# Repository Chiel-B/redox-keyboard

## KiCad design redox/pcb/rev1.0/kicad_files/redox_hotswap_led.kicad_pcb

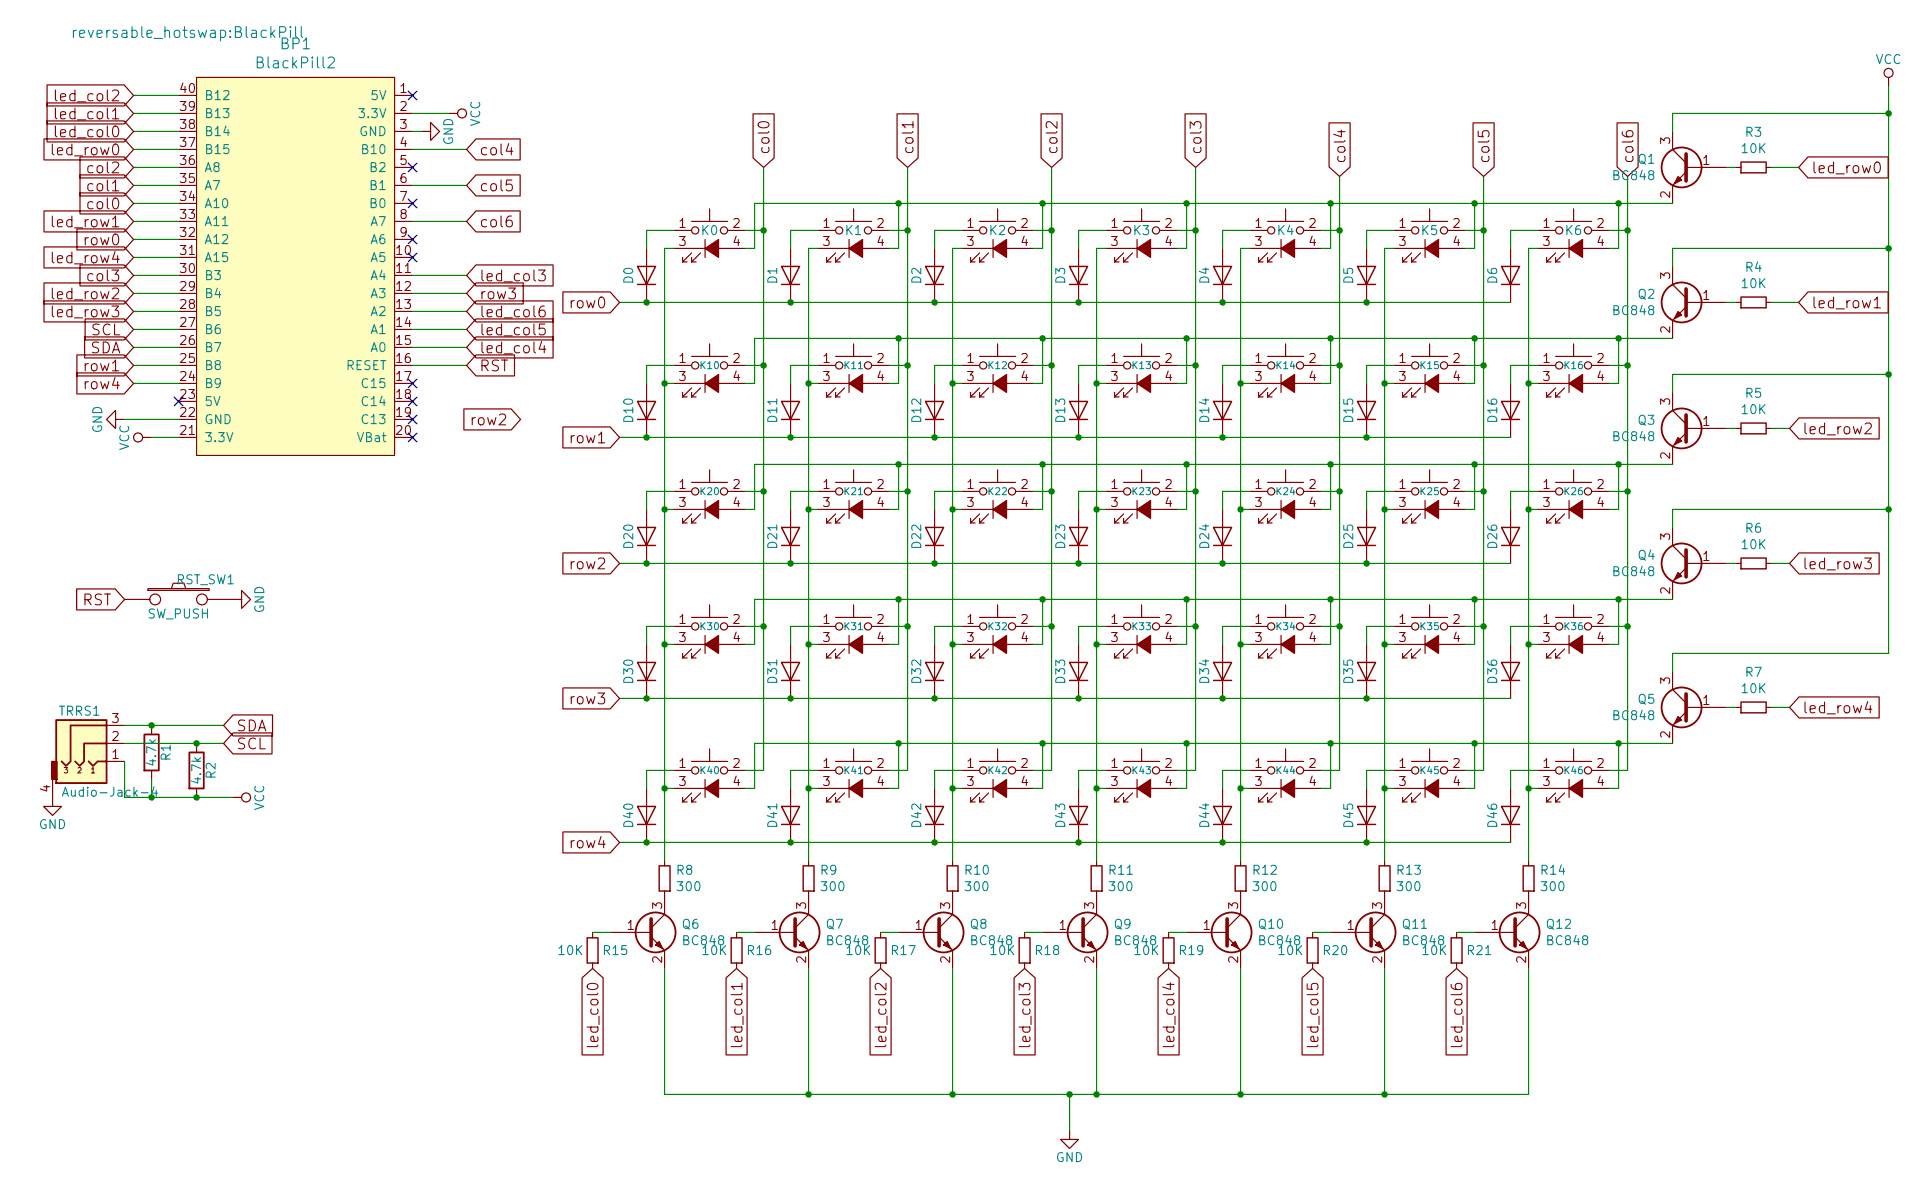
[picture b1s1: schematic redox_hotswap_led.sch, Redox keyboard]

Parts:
BP1: BlackPill2; BlackPill
D0, D1, D2, D3, D4, D5, D6, D10, D11, D12, D13, D14, D15, D16, D20, D21, D22, D23, D24, D25, D26, D30, D31, D32, D33, D34, D35, D36, D40, D41, D42, D43, D44, D45, D46: D; Diode-dual
K0, K10, K20, K30, K44: SW_Push_LED; MXOnly-1.25U-Hotswap
K1, K2, K4, K5, K6, K11, K12, K14, K15, K21, K22, K24, K25, K26, K31, K32, K33, K34, K35, K36, K40, K41, K42, K43: SW_Push_LED; MXOnly-1U-Hotswap
K3, K13, K23: SW_Push_LED; MXOnly-1U-Hotswap-Small
K16, K45, K46: SW_Push_LED; MXOnly-1.5U-Hotswap
Q1, Q2, Q3, Q4, Q5, Q6, Q7, Q8, Q9, Q10, Q11, Q12: BC848; SOT-23_Handsoldering_reversable
R1, R2: 4.7k; Resistor-dual
R3, R4, R5, R6, R7, R15, R16, R17, R18, R19, R20, R21: 10K; Resistor-dual
R8, R9, R10, R11, R12, R13, R14: 300; Resistor-dual
RST_SW1: SW_PUSH; SW_PUSH_6mm_h4.3mm
TRRS1: Audio-Jack-4; TRRS-PJ-320A-dual

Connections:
GND: BP1.3 (GND), BP1.22 (GND), Q6.2 (E), Q7.2 (E), Q8.2 (E), Q9.2 (E), Q10.2 (E), Q11.2 (E), Q12.2 (E), RST_SW1.2, TRRS1.4; also elsewhere on the board
unnamed: BP1.16 (RESET), RST_SW1.1
unnamed: D0.2 (A), K0.1
unnamed: D1.2 (A), K1.1
unnamed: D2.2 (A), K2.1
unnamed: D3.2 (A), K3.1
unnamed: D4.2 (A), K4.1
unnamed: D5.2 (A), K5.1
unnamed: D6.2 (A), K6.1
unnamed: D10.2 (A), K10.1
unnamed: D11.2 (A), K11.1
unnamed: D12.2 (A), K12.1
unnamed: D13.2 (A), K13.1
unnamed: D14.2 (A), K14.1
unnamed: D15.2 (A), K15.1
unnamed: D16.2 (A), K16.1
unnamed: D20.2 (A), K20.1
unnamed: D21.2 (A), K21.1
unnamed: D22.2 (A), K22.1
unnamed: D23.2 (A), K23.1
unnamed: D24.2 (A), K24.1
unnamed: D25.2 (A), K25.1
unnamed: D26.2 (A), K26.1
unnamed: D30.2 (A), K30.1
unnamed: D31.2 (A), K31.1
unnamed: D32.2 (A), K32.1
unnamed: D33.2 (A), K33.1
unnamed: D34.2 (A), K34.1
unnamed: D35.2 (A), K35.1
unnamed: D36.2 (A), K36.1
unnamed: D40.2 (A), K40.1
unnamed: D41.2 (A), K41.1
unnamed: D42.2 (A), K42.1
unnamed: D43.2 (A), K43.1
unnamed: D44.2 (A), K44.1
unnamed: D45.2 (A), K45.1
unnamed: D46.2 (A), K46.1
unnamed: K0.3 (K), K10.3 (K), K20.3 (K), K30.3 (K), K40.3 (K), R8.2
unnamed: K0.4 (A), K1.4 (A), K2.4 (A), K3.4 (A), K4.4 (A), K5.4 (A), K6.4 (A), Q1.2 (E)
unnamed: K1.3 (K), K11.3 (K), K21.3 (K), K31.3 (K), K41.3 (K), R9.2
unnamed: K10.4 (A), K11.4 (A), K12.4 (A), K13.4 (A), K14.4 (A), K15.4 (A), K16.4 (A), Q2.2 (E)
unnamed: K2.3 (K), K12.3 (K), K22.3 (K), K32.3 (K), K42.3 (K), R10.2
unnamed: K3.3 (K), K13.3 (K), K23.3 (K), K33.3 (K), K43.3 (K), R11.2
unnamed: K4.3 (K), K14.3 (K), K24.3 (K), K34.3 (K), K44.3 (K), R12.2
unnamed: K5.3 (K), K15.3 (K), K25.3 (K), K35.3 (K), K45.3 (K), R13.2
unnamed: K6.3 (K), K16.3 (K), K26.3 (K), K36.3 (K), K46.3 (K), R14.2
unnamed: K20.4 (A), K21.4 (A), K22.4 (A), K23.4 (A), K24.4 (A), K25.4 (A), K26.4 (A), Q3.2 (E)
unnamed: K30.4 (A), K31.4 (A), K32.4 (A), K33.4 (A), K34.4 (A), K35.4 (A), K36.4 (A), Q4.2 (E)
unnamed: K40.4 (A), K41.4 (A), K42.4 (A), K43.4 (A), K44.4 (A), K45.4 (A), K46.4 (A), Q5.2 (E)
unnamed: Q1.1 (B), R3.1
unnamed: Q2.1 (B), R4.1
unnamed: Q3.1 (B), R5.1
unnamed: Q4.1 (B), R6.1
unnamed: Q5.1 (B), R7.1
unnamed: Q6.1 (B), R15.2
unnamed: Q6.3 (C), R8.1
unnamed: Q7.1 (B), R16.2
unnamed: Q7.3 (C), R9.1
unnamed: Q8.1 (B), R17.2
unnamed: Q8.3 (C), R10.1
unnamed: Q9.1 (B), R18.2
unnamed: Q9.3 (C), R11.1
unnamed: Q10.1 (B), R19.2
unnamed: Q10.3 (C), R12.1
unnamed: Q11.1 (B), R20.2
unnamed: Q11.3 (C), R13.1
unnamed: Q12.1 (B), R21.2
unnamed: Q12.3 (C), R14.1
SCL: BP1.27 (B6), R2.1, TRRS1.2; also elsewhere on the board
SDA: BP1.26 (B7), R1.1, TRRS1.3; also elsewhere on the board
VCC: BP1.2 (3.3V), BP1.21 (3.3V), Q1.3 (C), Q2.3 (C), Q3.3 (C), Q4.3 (C), Q5.3 (C), R1.2, R2.2, TRRS1.1; also elsewhere on the board
col0: BP1.34 (A10), K0.2, K10.2, K20.2, K30.2, K40.2; also elsewhere on the board
col1: BP1.35 (A7), K1.2, K11.2, K21.2, K31.2, K41.2; also elsewhere on the board
col2: BP1.36 (A8), K2.2, K12.2, K22.2, K32.2, K42.2; also elsewhere on the board
col3: BP1.30 (B3), K3.2, K13.2, K23.2, K33.2, K43.2; also elsewhere on the board
col4: BP1.4 (B10), K4.2, K14.2, K24.2, K34.2, K44.2; also elsewhere on the board
col5: BP1.6 (B1), K5.2, K15.2, K25.2, K35.2, K45.2; also elsewhere on the board
col6: BP1.8 (A7), K6.2, K16.2, K26.2, K36.2, K46.2; also elsewhere on the board
led_col0: BP1.38 (B14), R15.1; also elsewhere on the board
led_col1: BP1.39 (B13), R16.1; also elsewhere on the board
led_col2: BP1.40 (B12), R17.1; also elsewhere on the board
led_col3: BP1.11 (A4), R18.1; also elsewhere on the board
led_col4: BP1.15 (A0), R19.1; also elsewhere on the board
led_col5: BP1.14 (A1), R20.1; also elsewhere on the board
led_col6: BP1.13 (A2), R21.1; also elsewhere on the board
led_row0: BP1.37 (B15), R3.2; also elsewhere on the board
led_row1: BP1.33 (A11), R4.2; also elsewhere on the board
led_row2: BP1.29 (B4), R5.2; also elsewhere on the board
led_row3: BP1.28 (B5), R6.2; also elsewhere on the board
led_row4: BP1.31 (A15), R7.2; also elsewhere on the board
row0: BP1.32 (A12), D0.1 (K), D1.1 (K), D2.1 (K), D3.1 (K), D4.1 (K), D5.1 (K), D6.1 (K); also elsewhere on the board
row1: BP1.25 (B8), D10.1 (K), D11.1 (K), D12.1 (K), D13.1 (K), D14.1 (K), D15.1 (K), D16.1 (K); also elsewhere on the board
row2: D20.1 (K), D21.1 (K), D22.1 (K), D23.1 (K), D24.1 (K), D25.1 (K), D26.1 (K)
row3: BP1.12 (A3), D30.1 (K), D31.1 (K), D32.1 (K), D33.1 (K), D34.1 (K), D35.1 (K), D36.1 (K); also elsewhere on the board
row4: BP1.24 (B9), D40.1 (K), D41.1 (K), D42.1 (K), D43.1 (K), D44.1 (K), D45.1 (K), D46.1 (K); also elsewhere on the board

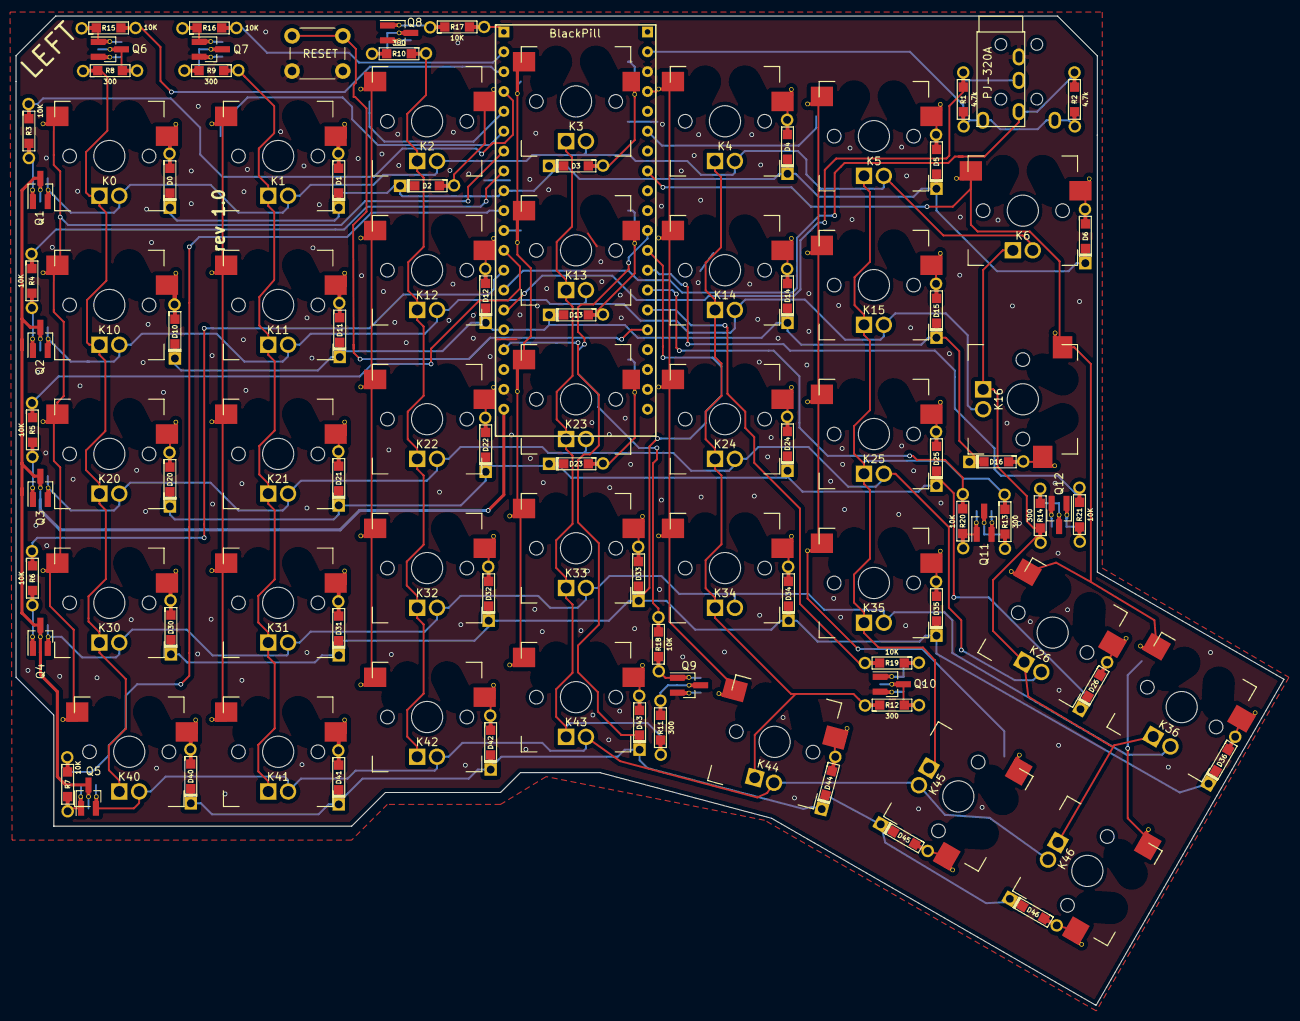
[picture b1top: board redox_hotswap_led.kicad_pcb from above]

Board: 2 copper layers, 162.2 x 126.5 mm, 106 parts (0 on the bottom side), 95 nets.

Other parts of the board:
BlackPill: BlackPill2; BlackPill
RESET: SW_PUSH; SW_PUSH_6mm_h4.3mm

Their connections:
GND: BlackPill.3, BlackPill.22, RESET.2; also elsewhere on the board
RST: BlackPill.16, RESET.1
SCL: BlackPill.27; also elsewhere on the board
SDA: BlackPill.26; also elsewhere on the board
VCC: BlackPill.2, BlackPill.21; also elsewhere on the board
col0: BlackPill.34; also elsewhere on the board
col1: BlackPill.35; also elsewhere on the board
col2: BlackPill.36; also elsewhere on the board
col3: BlackPill.30; also elsewhere on the board
col4: BlackPill.4; also elsewhere on the board
col5: BlackPill.6; also elsewhere on the board
col6: BlackPill.8; also elsewhere on the board
led_col0: BlackPill.38; also elsewhere on the board
led_col1: BlackPill.39; also elsewhere on the board
led_col2: BlackPill.40; also elsewhere on the board
led_col3: BlackPill.11; also elsewhere on the board
led_col4: BlackPill.15; also elsewhere on the board
led_col5: BlackPill.14; also elsewhere on the board
led_col6: BlackPill.13; also elsewhere on the board
led_row0: BlackPill.37; also elsewhere on the board
led_row1: BlackPill.33; also elsewhere on the board
led_row2: BlackPill.29; also elsewhere on the board
led_row3: BlackPill.28; also elsewhere on the board
led_row4: BlackPill.31; also elsewhere on the board
row0: BlackPill.32; also elsewhere on the board
row1: BlackPill.25; also elsewhere on the board
row3: BlackPill.12; also elsewhere on the board
row4: BlackPill.24; also elsewhere on the board

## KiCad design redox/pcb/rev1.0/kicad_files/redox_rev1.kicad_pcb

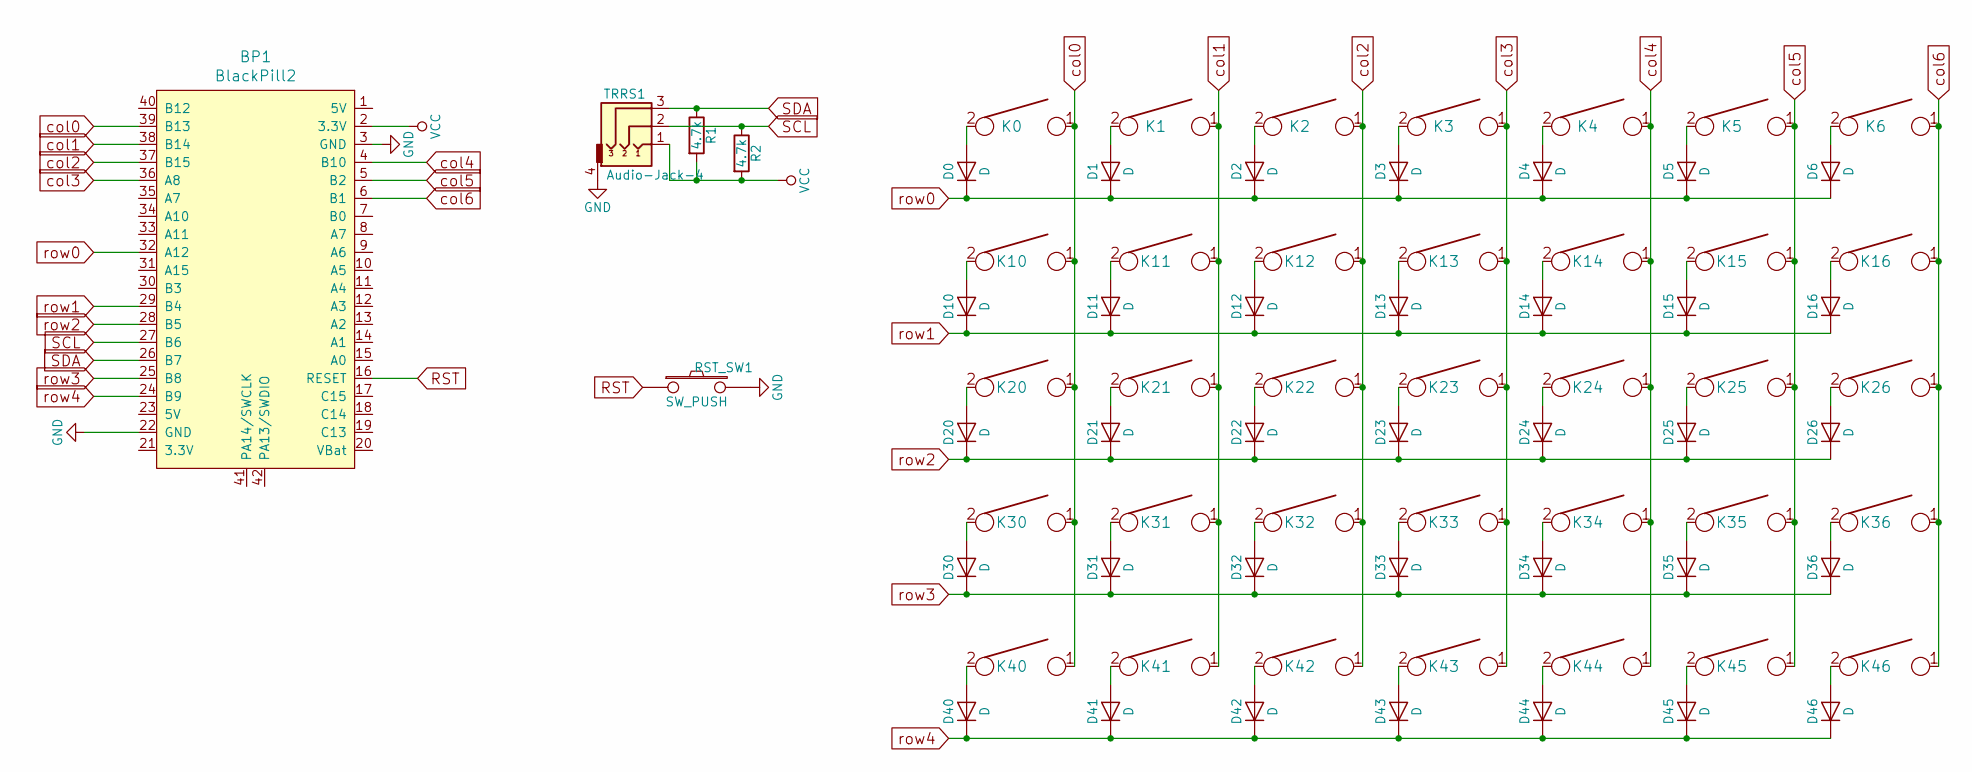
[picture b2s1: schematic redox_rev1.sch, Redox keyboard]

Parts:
BP1: BlackPill2; BlackPill
D0, D1, D2, D3, D4, D5, D6, D10, D11, D12, D13, D14, D15, D16, D20, D21, D22, D23, D24, D25, D26, D30, D31, D32, D33, D34, D35, D36, D40, D41, D42, D43, D44, D45, D46: D; Diode-dual
K0, K10, K20, K30, K44: KEYSW; MXOnly-1.25U-Hotswap
K1, K2, K4, K5, K6, K11, K12, K14, K15, K21, K22, K24, K25, K26, K31, K32, K33, K34, K35, K36, K40, K41, K42, K43: KEYSW; MXOnly-1U-Hotswap
K3, K13, K23: KEYSW; MXOnly-1U-Hotswap-Small
K16, K45, K46: KEYSW; MXOnly-1.5U-Hotswap
R1, R2: 4.7k; Resistor-Compact
RST_SW1: SW_PUSH; SW_PUSH_6mm_h4.3mm
TRRS1: Audio-Jack-4; TRRS-PJ-320A-dual

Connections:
GND: BP1.3 (GND), BP1.22 (GND), RST_SW1.2, TRRS1.4
unnamed: D0.2 (A), K0.2
unnamed: D1.2 (A), K1.2
unnamed: D2.2 (A), K2.2
unnamed: D3.2 (A), K3.2
unnamed: D4.2 (A), K4.2
unnamed: D5.2 (A), K5.2
unnamed: D6.2 (A), K6.2
unnamed: D10.2 (A), K10.2
unnamed: D11.2 (A), K11.2
unnamed: D12.2 (A), K12.2
unnamed: D13.2 (A), K13.2
unnamed: D14.2 (A), K14.2
unnamed: D15.2 (A), K15.2
unnamed: D16.2 (A), K16.2
unnamed: D20.2 (A), K20.2
unnamed: D21.2 (A), K21.2
unnamed: D22.2 (A), K22.2
unnamed: D23.2 (A), K23.2
unnamed: D24.2 (A), K24.2
unnamed: D25.2 (A), K25.2
unnamed: D26.2 (A), K26.2
unnamed: D30.2 (A), K30.2
unnamed: D31.2 (A), K31.2
unnamed: D32.2 (A), K32.2
unnamed: D33.2 (A), K33.2
unnamed: D34.2 (A), K34.2
unnamed: D35.2 (A), K35.2
unnamed: D36.2 (A), K36.2
unnamed: D40.2 (A), K40.2
unnamed: D41.2 (A), K41.2
unnamed: D42.2 (A), K42.2
unnamed: D43.2 (A), K43.2
unnamed: D44.2 (A), K44.2
unnamed: D45.2 (A), K45.2
unnamed: D46.2 (A), K46.2
RST: BP1.16 (RESET), RST_SW1.1
SCL: BP1.27 (B6), R2.1, TRRS1.2
SDA: BP1.26 (B7), R1.1, TRRS1.3
VCC: BP1.2 (3.3V), R1.2, R2.2, TRRS1.1
col0: BP1.39 (B13), K0.1, K10.1, K20.1, K30.1, K40.1
col1: BP1.38 (B14), K1.1, K11.1, K21.1, K31.1, K41.1
col2: BP1.37 (B15), K2.1, K12.1, K22.1, K32.1, K42.1
col3: BP1.36 (A8), K3.1, K13.1, K23.1, K33.1, K43.1
col4: BP1.4 (B10), K4.1, K14.1, K24.1, K34.1, K44.1
col5: BP1.5 (B2), K5.1, K15.1, K25.1, K35.1, K45.1
col6: BP1.6 (B1), K6.1, K16.1, K26.1, K36.1, K46.1
row0: BP1.32 (A12), D0.1 (K), D1.1 (K), D2.1 (K), D3.1 (K), D4.1 (K), D5.1 (K), D6.1 (K)
row1: BP1.29 (B4), D10.1 (K), D11.1 (K), D12.1 (K), D13.1 (K), D14.1 (K), D15.1 (K), D16.1 (K)
row2: BP1.28 (B5), D20.1 (K), D21.1 (K), D22.1 (K), D23.1 (K), D24.1 (K), D25.1 (K), D26.1 (K)
row3: BP1.25 (B8), D30.1 (K), D31.1 (K), D32.1 (K), D33.1 (K), D34.1 (K), D35.1 (K), D36.1 (K)
row4: BP1.24 (B9), D40.1 (K), D41.1 (K), D42.1 (K), D43.1 (K), D44.1 (K), D45.1 (K), D46.1 (K)

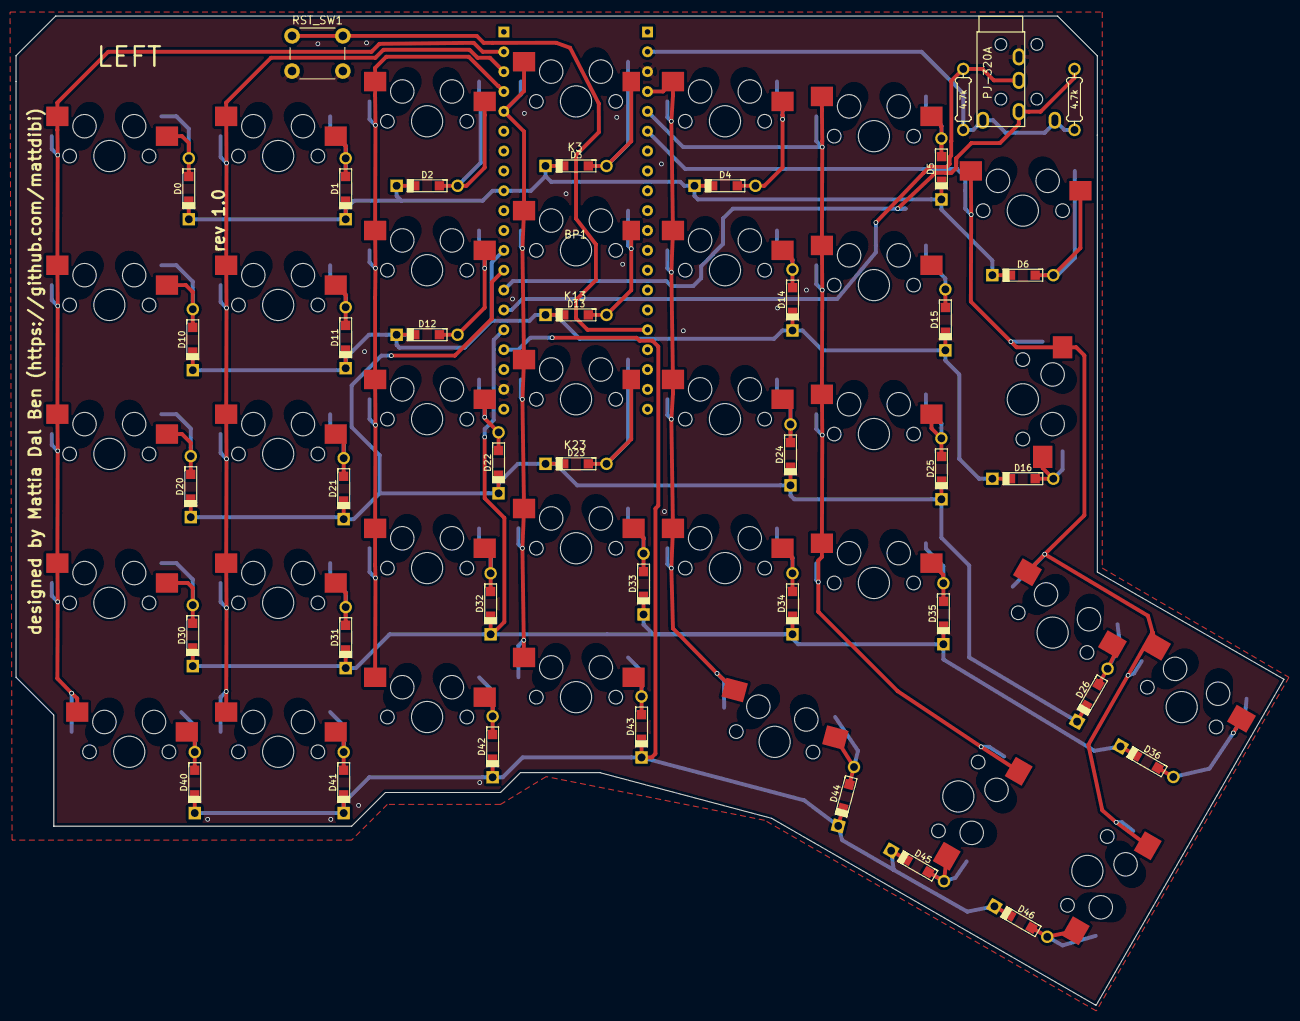
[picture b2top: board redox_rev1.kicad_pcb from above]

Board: 2 copper layers, 162.2 x 126.5 mm, 75 parts (0 on the bottom side), 52 nets.

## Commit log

2020-02-20 Add MX_Alps components
2020-02-20 Move into kicad libs folder
2020-02-20 Add kicad_lib_tmk
2020-02-20 Add keebio-components library
2020-02-20 Relative path to libraries
2020-02-20 Add keyboards_parts lib
2020-02-23 Update to reversible kailh hotswap
2020-03-01 Finish routing and top silkscreen
2020-03-05 Complete routing and PCB
2021-06-05 Add redox firmware
